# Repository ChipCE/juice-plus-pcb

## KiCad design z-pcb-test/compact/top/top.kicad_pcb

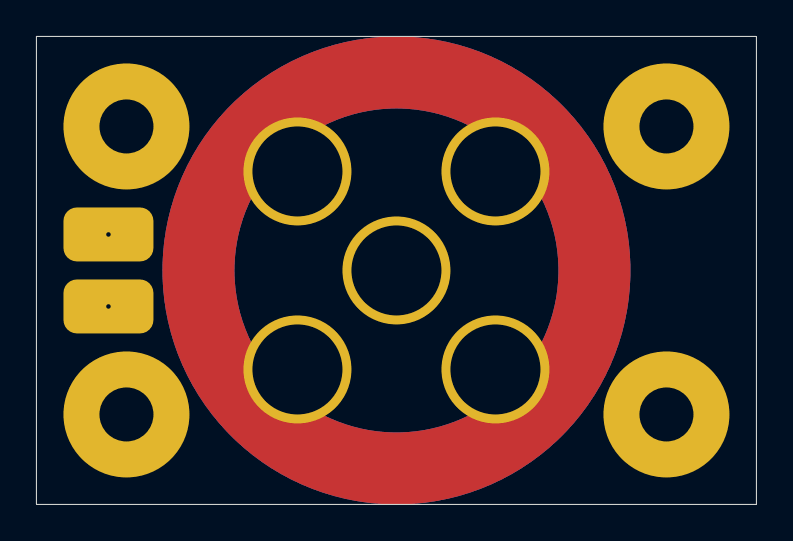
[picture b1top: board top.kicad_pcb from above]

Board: 4 copper layers, 40.0 x 26.0 mm, 6 parts (0 on the bottom side), 2 nets, no tracks yet.

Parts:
J1: Conn_01x02_Female; solder-pin-th-2pin
J2, J3, J4, J5: BOLT-HOLE; m3-d7-mounting-hole
J6: DRAGON-HOTEND-SLOT; dragon-hotend-cutout

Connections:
unnamed: J1.1, J6.1
unnamed: J1.2, J2.1, J3.1, J4.1, J5.1

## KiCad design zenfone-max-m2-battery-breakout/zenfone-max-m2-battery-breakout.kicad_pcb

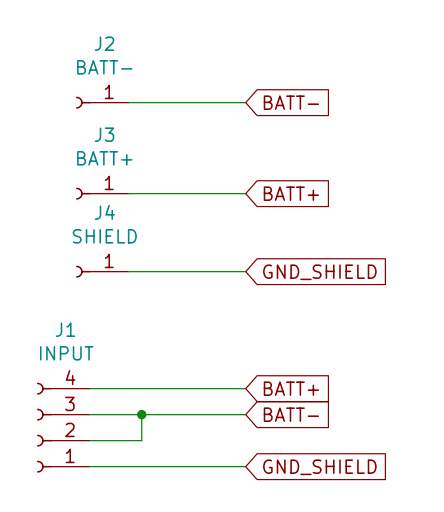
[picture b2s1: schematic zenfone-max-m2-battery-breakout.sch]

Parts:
J1: INPUT; molex_1x4_smd
J2: BATT-; solder-pad
J3: BATT+; solder-pad
J4: SHIELD; solder-pad

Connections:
BATT+: J1.4, J3.1
BATT-: J1.2, J1.3, J2.1
GND_SHIELD: J1.1, J4.1

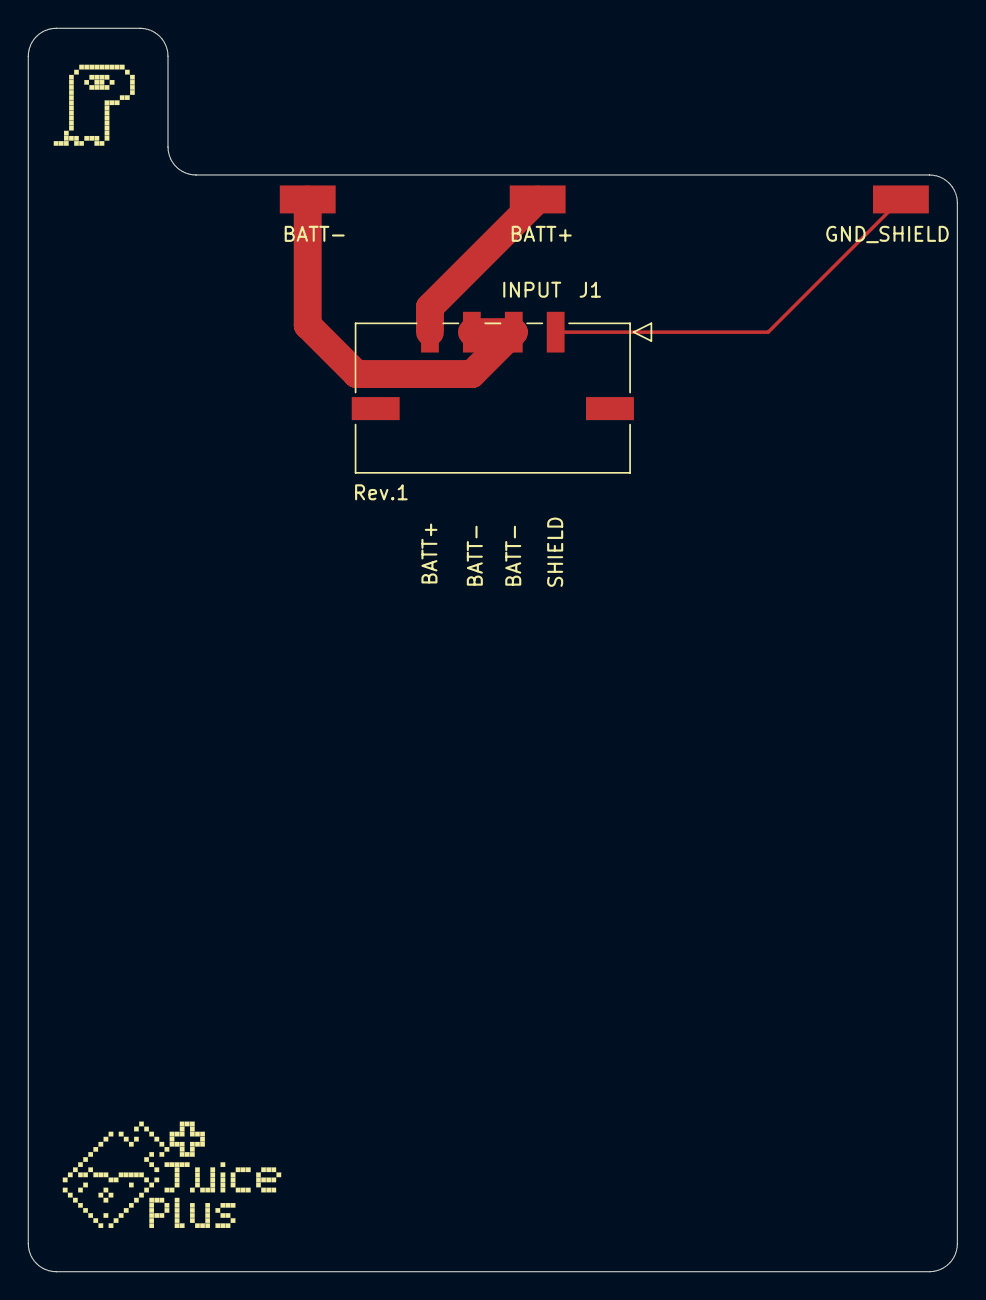
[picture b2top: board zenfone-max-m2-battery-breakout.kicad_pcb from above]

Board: 2 copper layers, 66.5 x 89.0 mm, 4 parts (0 on the bottom side), 3 nets.

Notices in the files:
parts and their libraries:
Copyright 2021 Accelerated Designs. All rights reserved.
